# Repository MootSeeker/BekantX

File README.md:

# BekantX

## Documentation

- [Requirements specification](Docs/description.md)
- [System architecture](Docs/architecture.md)
- [Inter-controller SPI protocol](Docs/inter-controller-protocol.md)
- [IKEA BEKANT LIN protocol](Docs/bekant-lin-protocol.md)

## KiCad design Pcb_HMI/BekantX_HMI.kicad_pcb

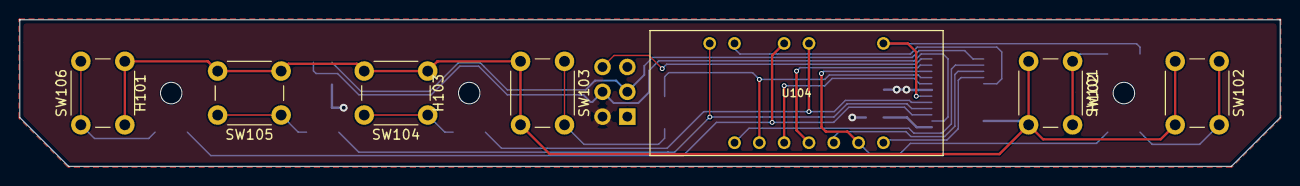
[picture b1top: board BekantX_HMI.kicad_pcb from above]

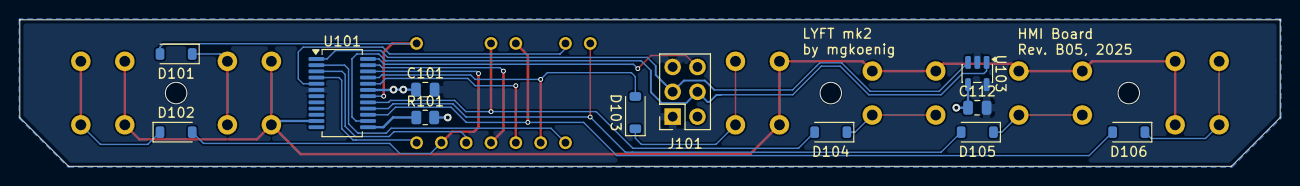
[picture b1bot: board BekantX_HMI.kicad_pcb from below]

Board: 2 copper layers, 129.0 x 15.0 mm, 22 parts (12 on the bottom side), 19 nets.

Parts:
C101: 10u; C_0805_2012Metric
C112: 100n; C_0805_2012Metric
D101, D102, D103, D104, D105, D106: 1N4148W; D_SOD-123
H101, H102, H103: MountingHole; MountingHole_2.2mm_M2
J101: Conn_HMI; PinSocket_2x03_P2.54mm_Vertical
R101: 13k; R_0805_2012Metric
SW101, SW102, SW103, SW104, SW105, SW106: SW_Omron_B3FS; SW_PUSH_6mm
U101: AS1115-BSST; QSOP-24_3.9x8.7mm_P0.635mm
U103: 24FC01T; SOT-23-5
U104: HDSP-433G

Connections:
+3V3: C101.1, C112.1, J101.2, R101.2, U101.19 (VDD), U103.4 (VCC)
GND: C101.2, C112.2, J101.1, J101.5, U101.6 (GND), U103.2 (GND), U103.5 (WP)
HMI_IRQ: J101.6, U101.24 (IRQ)
I2C_SCL: J101.4, U101.14 (SCL), U103.1 (SCL)
I2C_SDA: J101.3, U101.1 (SDA), U103.3 (SDA)
KEY_A: SW101.2, SW102.2, SW103.2, SW104.2, SW105.2, SW106.2, U101.11 (KEYA)
unnamed: D101.1 (K), SW101.1
unnamed: D102.1 (K), SW102.1
unnamed: D103.1 (K), SW103.1
unnamed: D104.1 (K), SW104.1
unnamed: D105.1 (K), SW105.1
unnamed: D106.1 (K), SW106.1
unnamed: R101.1, U101.13 (ISET)
SEG_A: D106.2 (A), U101.15 (SEGA)
SEG_B: D104.2 (A), U101.17 (SEGB)
SEG_DP: D102.2 (A), U101.22 (SEGDP)
SEG_E: D103.2 (A), U101.21 (SEGE)
SEG_F: D105.2 (A), U101.16 (SEGF)
SEG_G: D101.2 (A), U101.18 (SEGG)

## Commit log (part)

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2026-04-16 Add documentation for BekantX project including LIN protocol, requirements, and inter-controller protocol
    - Introduced `bekant-lin-protocol.md` detailing the reverse-engineered LIN protocol for the IKEA BEKANT desk, covering bus characteristics, frame model, node map, runtime payload formats, and known c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
    - Created `description.md` outlining the BekantX requirements specification, including purpose, scope, architectural requirements, functional requirements, safety and fault handling, and non-function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
    - Established `inter-controller-protocol.md` to define the message-level protocol between the primary and secondary controllers, detailing transport definition, fr
2026-04-16 Add initial KiCad project files and .gitignore
2026-04-17 Add KiCad Project
2026-04-17 Update Schematic
2026-04-18 Split Project into two PCBs. HMI PCB now has an OLED Display. Controller PCB is now steered by STM32 uC and uses ESP32-C3 as networking Module with inter CPU protocol.
2026-04-18 Work
2026-04-19 work on HMI
2026-04-22 minor changes - added test points
2026-04-22 Add some Test points
2026-04-22 Add Case
2026-04-22 Add Wi-Fi FTM example for ESP32-C3
    - Created CMakeLists.txt to define project structure.
    - Added main application code in ftm_main.c for FTM (Fine Timing Measurement) functionality.
    - Implemented command-line interface for Wi-Fi station and access point modes, including FTM initiator and responder commands.
    - Introduced configuration options in Kconfig.projbuild for enabling FTM report logging.
    - Added necessary JSON configuration files for Visual Studio Code integration.
    - Updated README.md with detailed usage instructions for the FTM example.
2026-04-23 chore: consolidate code change entries for better organization
2026-04-25 Refactor Wi-Fi FTM example: separate app_main into ftm_app_start and add header file
2026-04-25 feat(led): add WS2812 RGB LED driver with breath animation
    - Add ws2812_transport (C/RMT backend, GPIO18, 10 MHz, GRB order)
    - Add LedDriver C++ class (pixel buffer, brightness scaling, Show/Clear)
    - Add LedAnimator C++ state machine (Blink, FadeIn/Out, FadeInOut, Breath)
    - Add LED_BREATH mode: cubic smooth-step 0->max->0, flicker-free at wrap
    - Add StatusIndicator mapping DeviceStatus to LED patterns
    - Boot pattern: yellow LED_BREATH, period 2 s, brightness 0-100
2026-04-25 feat: enhance application and status indicator classes with detailed documentation and improve configuration paths
2026-04-25 refactor: remove unused core component and clean up application structure
2026-04-25 chore: update .gitignore to exclude all VSCode configuration files
2026-04-30 feat: Add MQTT service for BekantX desk control
    - Introduced MQTT service to manage communication with Home Assistant.
    - Added configuration options for MQTT broker URI, device ID, and topics.
    - Implemented MQTT command handling, state publishing, and auto-discovery for Home Assistant.
    - Integrated deep sleep functionality with configurable wake GPIO.
    - Created necessary classes for handling MQTT credentials, commands, state, and discovery.
    - Updated Kconfig to include new MQTT and deep sleep options.
2026-04-30 feat: Enhance WiFiManager and MQTT service with atomic variables and improved logging
